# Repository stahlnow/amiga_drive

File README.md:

This is a SMD board layout for the amiga pi drive from Maurizio Ramondo
http://amigadrive.blogspot.ch/

# BOM

| Part                     | Value                | Package     | Description                                        |
|--------------------------|----------------------|-------------|----------------------------------------------------|
| BUTTONS                  | gnd | chg | wrt      | 1X03        | Pin Header                                         |
| C1                       | 10uF                 | PANASONIC_B | Electrolytic Capacitor                             |
| C2                       | 100nF                | 1206        | Capacitor                                          |
| C3                       | 220pf                | 1206        | Capacitor                                          |
| "D1 – D5, D7"            | SB140                | DO41-10     | Schottky Diode                                     |
| D6                       | 1N4148               | SOD-123     | Diode                                              |
| IC1                      | 74LS06D              | SO14        | "Hex INVERTER, open collector high-voltage output" |
| JP1                      | Amiga Floppy Power   | 1X04/90     | Pin Header                                         |
| JP2                      | Amiga Internal Drive | 2X17        | Pin Header                                         |
| JP3                      | Raspberry PI         | RPI_P1      | Pin Header                                         |
| LED1                     | BLUE                 | LED3MM      | LED                                                |
| R1 – R7                  | 1k                   | 1206        | Resistor                                           |
| "R8, R14, R16, R26, R27" | 4k7                  | 1206        | Resistor                                           |
| "R9 – R13, R17, R18"     | 2k7                  | 1206        | Resistor                                           |
| R15                      | 10k                  | 1206        | Resistor                                           |
| R19 – R25                | 6k8                  | 1206        | Resistor                                           |
| R28                      | 330                  | 1206        | Resistor                                           |
| S1                       | SEL1                 | DS-01       | Switch                                             |

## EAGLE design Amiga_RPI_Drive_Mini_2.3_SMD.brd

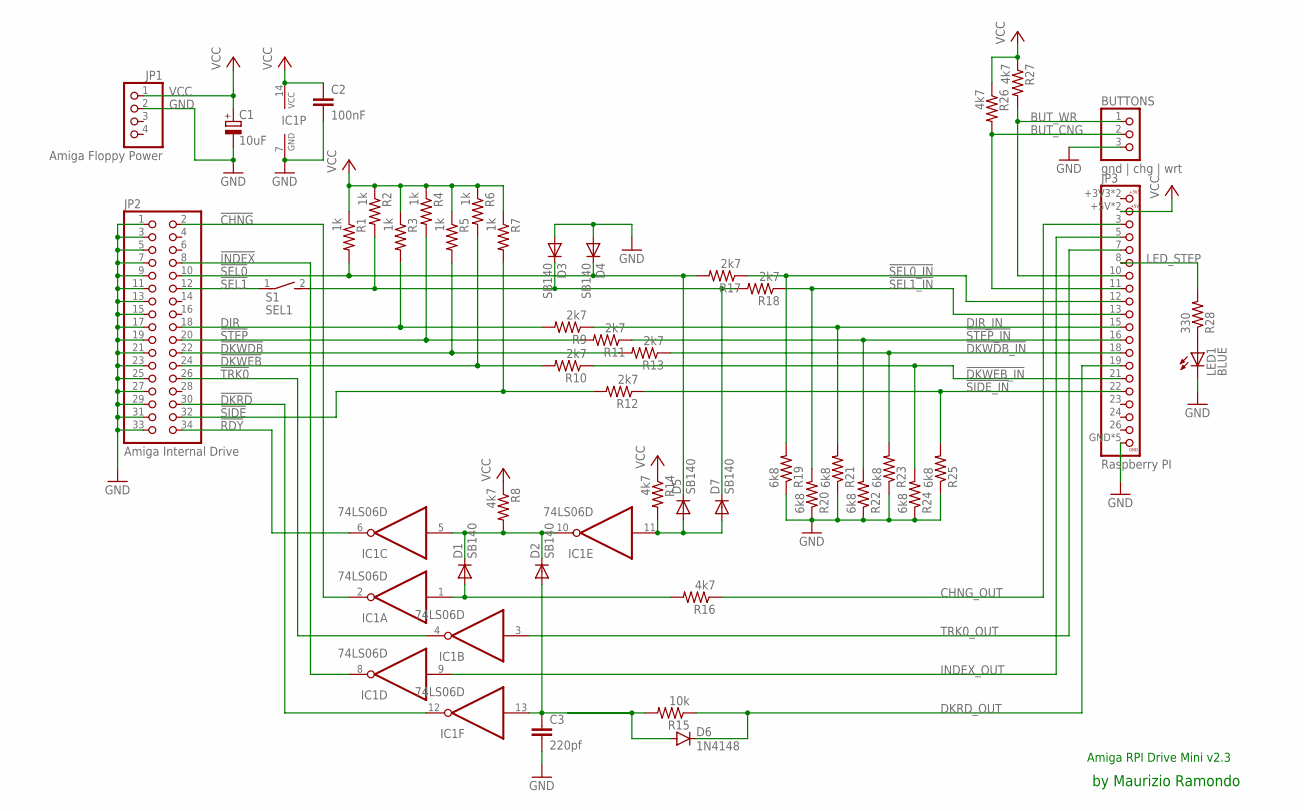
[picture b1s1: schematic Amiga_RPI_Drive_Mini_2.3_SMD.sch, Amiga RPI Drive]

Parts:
BUTTONS: gnd | chg | wrt; 1X03
C1: 10uF; PANASONIC_B
C2: 100nF; 1206
C3: 220pf; 1206
D1, D2, D3, D4, D5, D7: SB140; DO41-10
D6: 1N4148; SOD-123
IC1: 74LS06D; SO14
JP1: Amiga Floppy Power; 1X04/90
JP2: Amiga Internal Drive; 2X17
JP3: Raspberry PI; RPI_P1
LED1: BLUE; LED3MM
R1, R2, R3, R4, R5, R6, R7: 1k; 1206
R8, R14, R16, R26, R27: 4k7; 1206
R9, R10, R11, R12, R13, R17, R18: 2k7; 1206
R15: 10k; 1206
R19, R20, R21, R22, R23, R24, R25: 6k8; 1206
R28: 330; 1206
S1: SEL1; DS-01

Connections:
!CHNG: IC1.2 (O), JP2.2
!DKRD: IC1.12 (O), JP2.30
!DKWDB: JP2.22, R5.2, R13.2
!DKWDB_IN: JP3.18, R13.1, R23.2
!DKWEB: JP2.24, R6.2, R10.2
!DKWEB_IN: JP3.21, R10.1, R24.2
!INDEX: IC1.8 (O), JP2.8
!RDY: IC1.6 (O), JP2.34
!SEL0: D4.C, D5.C, JP2.10, R1.2, R17.2
!SEL0_IN: JP3.12, R17.1, R19.2
!SEL1: D3.C, D7.C, R2.2, R18.2, S1.2
!SEL1_IN: JP3.13, R18.1, R20.2
!SIDE: JP2.32, R7.2, R12.2
!SIDE_IN: JP3.22, R12.1, R25.2
!STEP: JP2.20, R4.2, R11.2
!STEP_IN: JP3.16, R11.1, R22.2
!TRK0: IC1.4 (O), JP2.26
BUT_CNG: BUTTONS.2, JP3.11, R26.2
BUT_WR: BUTTONS.1, JP3.10, R27.2
CHNG_OUT: JP3.3, R16.1
DIR: JP2.18, R3.2, R9.2
DIR_IN: JP3.15, R9.1, R21.2
DKRD_OUT: D6.C, JP3.19, R15.1
GND: BUTTONS.3, C1.-, C2.2, C3.2, D3.A, D4.A, IC1.7 (GND), JP1.2, JP2.1, JP2.3, JP2.5, JP2.7, JP2.9, JP2.11, JP2.13, JP2.15, JP2.17, JP2.19, JP2.21, JP2.23, JP2.25, JP2.27, JP2.29, JP2.31, JP2.33, JP3.GND, JP3.GND@9 (GND), JP3.GND@14 (GND), JP3.GND@20 (GND), JP3.GND@25 (GND), LED1.K (C), R19.1, R20.1, R21.1, R22.1, R23.1, R24.1, R25.1
INDEX_OUT: IC1.9 (I), JP3.5
LED_STEP: JP3.8, R28.2
unnamed: D1.A, IC1.1 (I), R16.2
unnamed: LED1.A, R28.1
unnamed: D5.A, D7.A, IC1.11 (I), R14.2
unnamed: C3.1, D2.A, D6.A, IC1.13 (I), R15.2
unnamed: D1.C, D2.C, IC1.5 (I), IC1.10 (O), R8.2
unnamed: JP2.12, S1.1
TRK0_OUT: IC1.3 (I), JP3.7
VCC: C1.+, C2.1, IC1.14 (VCC), JP1.1, JP3.4 (2), JP3.+5V (2), R1.1, R2.1, R3.1, R4.1, R5.1, R6.1, R7.1, R8.1, R14.1, R26.1, R27.1

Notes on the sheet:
Amiga RPI Drive Mini v2.3
by Maurizio Ramondo

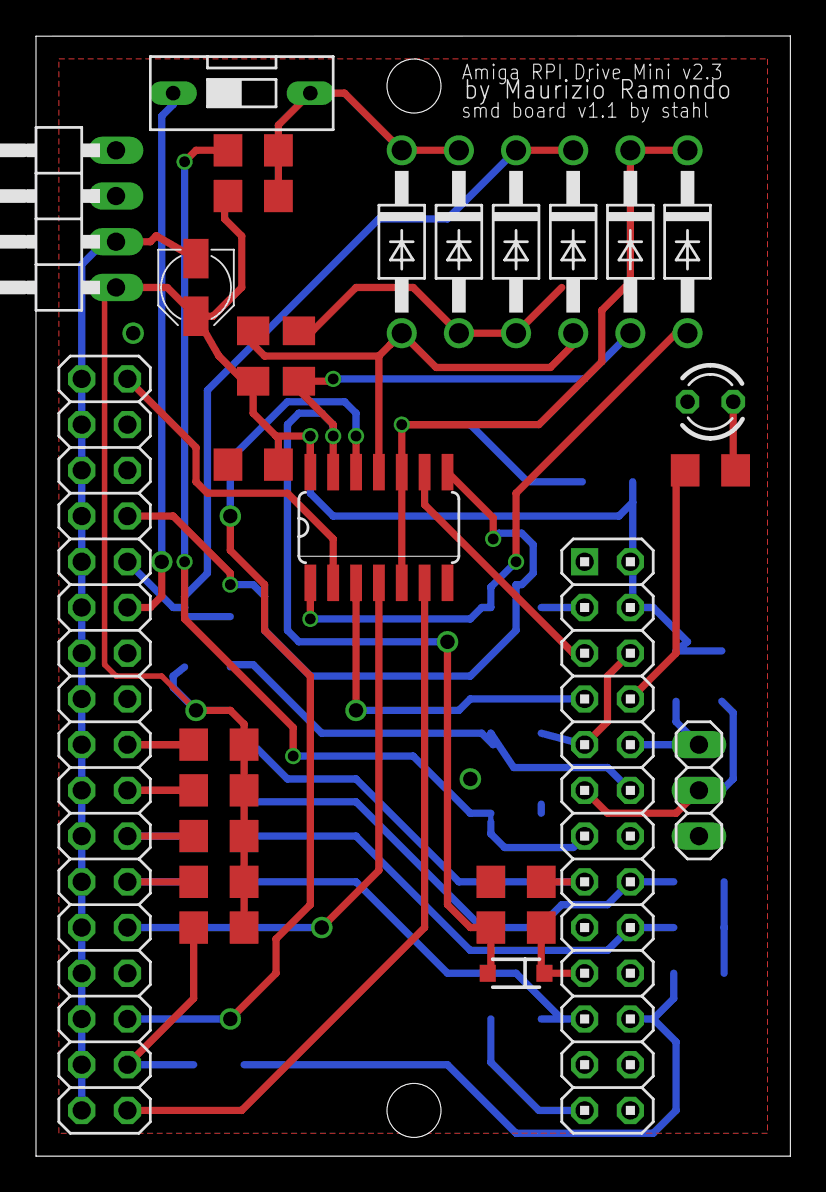
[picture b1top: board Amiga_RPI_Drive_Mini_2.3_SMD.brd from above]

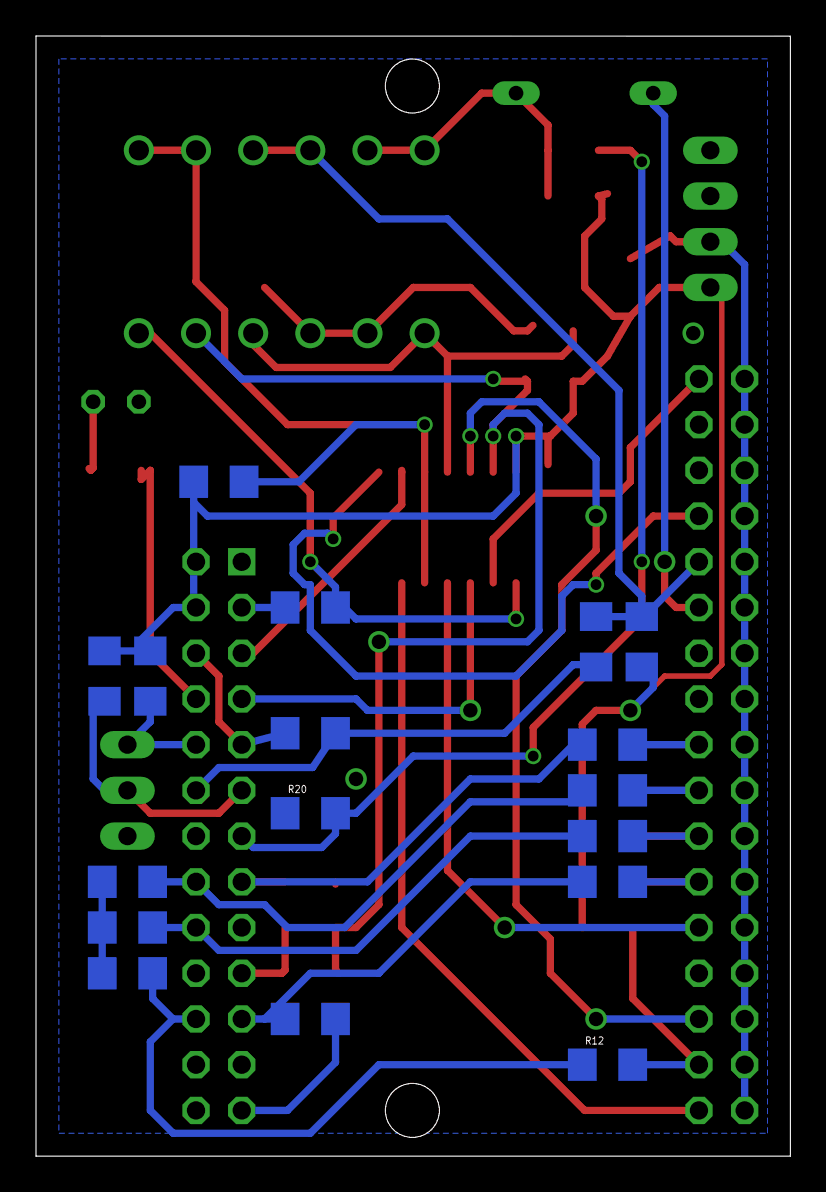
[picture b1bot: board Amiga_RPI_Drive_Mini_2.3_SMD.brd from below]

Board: 2 copper layers, 41.9 x 62.2 mm, 45 parts (17 on the bottom side), 34 nets.

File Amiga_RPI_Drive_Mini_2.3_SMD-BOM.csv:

Part,Value,Device,Package,Description
C1,10uF,CPOL-EUB,PANASONIC_B,"POLARIZED CAPACITOR, European symbol"
C2,100nF,CAP1206,1206,Capacitor
C3,220pf,CAP1206,1206,Capacitor
"D1 – D5, D7",B340A,DIODE-SCHOTTKY-B340A,SMA-DIODE,Schottky diodes in SFE's production catalog
D6,1N4148,DIODESOD123,SOD-123,Diode
IC1,74LS06D,74LS06D,SO14,"Hex INVERTER, open collector high-voltage output"
LED1,BLUE,LED-BLUE1206,LED-1206,Blue LEDs for production use
R1 – R7,1k,RESISTOR1206,1206,Resistor
"R8, R14, R16, R26, R27",4k7,RESISTOR1206,1206,Resistor
"R9 – R13, R17, R18",2k7,RESISTOR1206,1206,Resistor
R15,10k,RESISTOR1206,1206,Resistor
R19 – R25,6k8,RESISTOR1206,1206,Resistor
R28,330,RESISTOR1206,1206,Resistor
S1,SEL1,DS01E,DS-01,DIL/CODE SWITCH
BUTTONS,gnd | chg | wrt,PINHD-1X3,1X03,PIN HEADER
JP1,Amiga Floppy Power,PINHD-1X4/90,1X04/90,PIN HEADER
JP2,Amiga Internal Drive,PINHD-2X17,2X17,PIN HEADER
JP3,Raspberry PI,RPI_P1,RPI_P1,PIN HEADER

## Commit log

2017-05-14 born :rocket:
2017-05-14 :cake:
2017-05-16 BOM :bomb:
2017-06-09 :camera: add placment
2017-08-18 :punch: fixed diodes - v1.1
2017-08-18 :punch: v1.1
2021-11-24 :art: pdf

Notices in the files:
parts and their libraries:
SparkFun-Capacitors: Licensing: Creative Commons ShareAlike 4.0 International - https://creativecommons.org/licenses/by-sa/4.0
